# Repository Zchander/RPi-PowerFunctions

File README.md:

RPi-PowerFunctions
==================

A project to send commands over IR to a LEGO PowerFunctions receiver using an Raspberry Pi, I2C and an ATtiny2313

The Eagle project files have been added (including the PCB designs), as are the XMLRPC server files.

I'll try to update/create READMEs for the sub folders in the near future. Unfortunately my documenting skills are a bit 'subzero'

For this project I would like to thank a few people, who I will list down here. Please note that the order is random!
- Jurriaan Pruis (https://github.com/jurriaan/) for his project which gave me the idea(s)
- Dick de Wit (www.dansendelichtjes.nl) who helped me refresh some of my electronics skills
- A few from www.avrfreaks.net, some I will mention explicit:
- - kk6gm for inspiring me to NOT use _delay_ms/_delay_us in my code, but to use interrupts
- - kartman for his tutorial on multitasking on the AVR environment
- - david.prentice for directing me into a bug I introduced myself during code cleanup
- - clawson for his inspiring and helpful comments overall

(If I forgot someone, please let me know so I can include you on the list)

Xander

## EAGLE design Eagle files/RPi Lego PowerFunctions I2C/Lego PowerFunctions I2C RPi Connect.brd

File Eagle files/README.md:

The Eagle file(s) are made with version 7.2.0 and only contain the schematics. The PCB designs still have to be made.

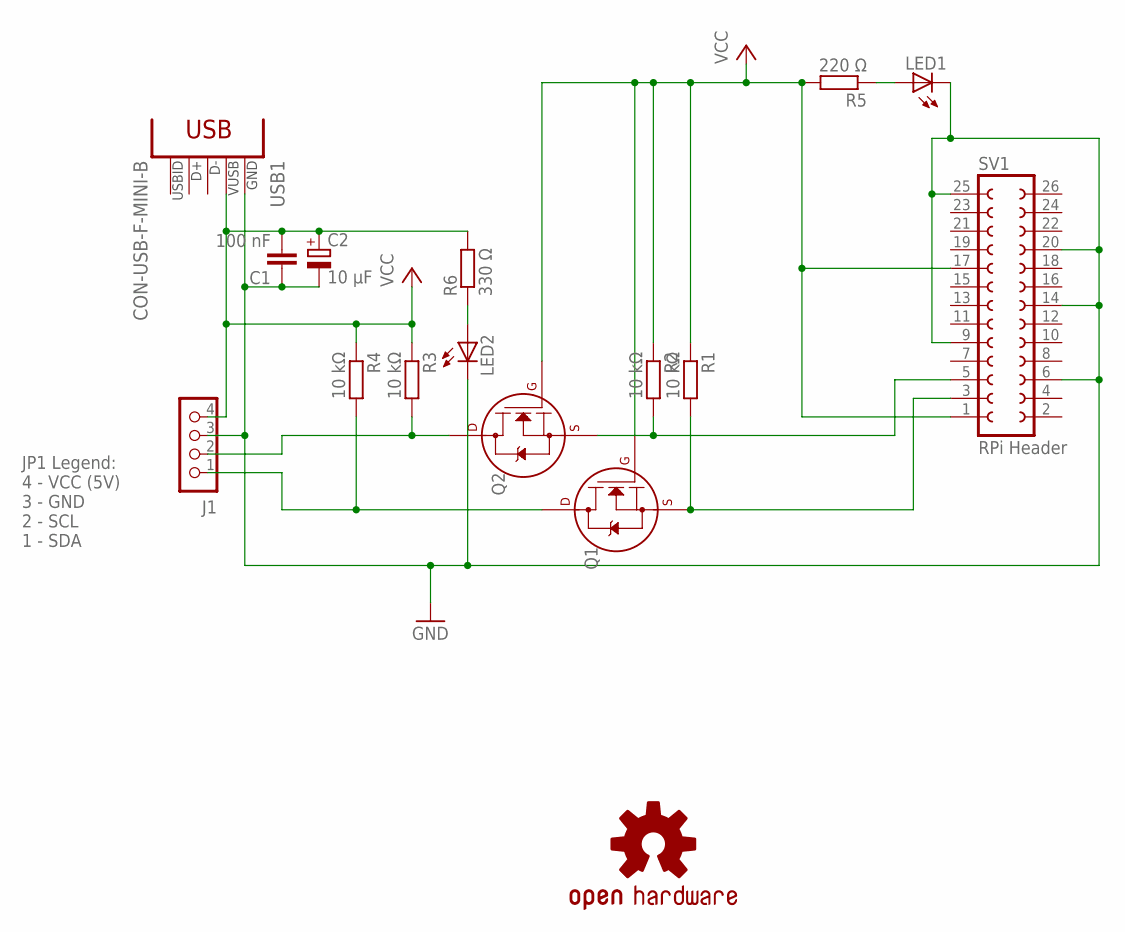
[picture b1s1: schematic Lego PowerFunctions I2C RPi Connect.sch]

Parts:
C1: 100 nF; C025-025X050
C2: 10 µF; E2,5-6
J1: CON_HEADER_1X04; M1X4
LED1, LED2: LED3MM
LOGO1: OSHW-LOGOL; OSHW-LOGO-L
Q1, Q2: 2N7000_TO92; TO-92
R1, R2, R3, R4: 10 kΩ; 0207/10
R5: 220 Ω; 0207/10
R6: 330 Ω; 0207/10
SV1: RPi Header; FE13-2
USB1: CON-USB-F-MINI-B; CONN_USB_MINI-B

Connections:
GND: C1.1, C2.-, J1.3, LED1.K (C), LED2.K (C), SV1.6, SV1.9, SV1.14, SV1.20, SV1.25, USB1.GND
unnamed: LED1.A, R5.1
unnamed: LED2.A, R6.1
unnamed: Q1.1 (S), R1.2, SV1.3
SCL_HV: J1.2, Q2.3 (D), R3.2
SCL_LV: Q2.1 (S), R2.2, SV1.5
SDA_HV: J1.1, Q1.3 (D), R4.2
VCC_HV: C1.2, C2.+, J1.4, R3.1, R4.1, R6.2, USB1.VUSB
VCC_LV: Q1.2 (G), Q2.2 (G), R1.1, R2.1, R5.2, SV1.1, SV1.17

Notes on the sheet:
JP1 Legend: 4 - VCC (5V) 3 - GND 2 - SCL 1 - SDA

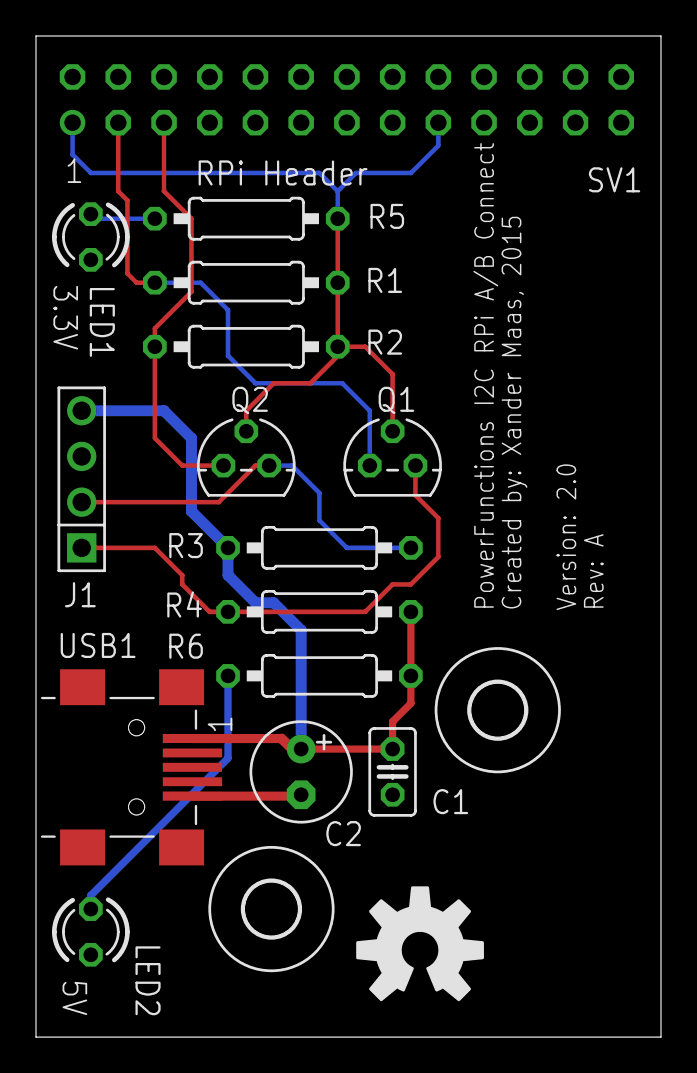
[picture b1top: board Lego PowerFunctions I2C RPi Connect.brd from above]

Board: 2 copper layers, 34.7 x 55.6 mm, 18 parts (1 on the bottom side), 9 nets.

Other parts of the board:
U$1, U$3: 3,0

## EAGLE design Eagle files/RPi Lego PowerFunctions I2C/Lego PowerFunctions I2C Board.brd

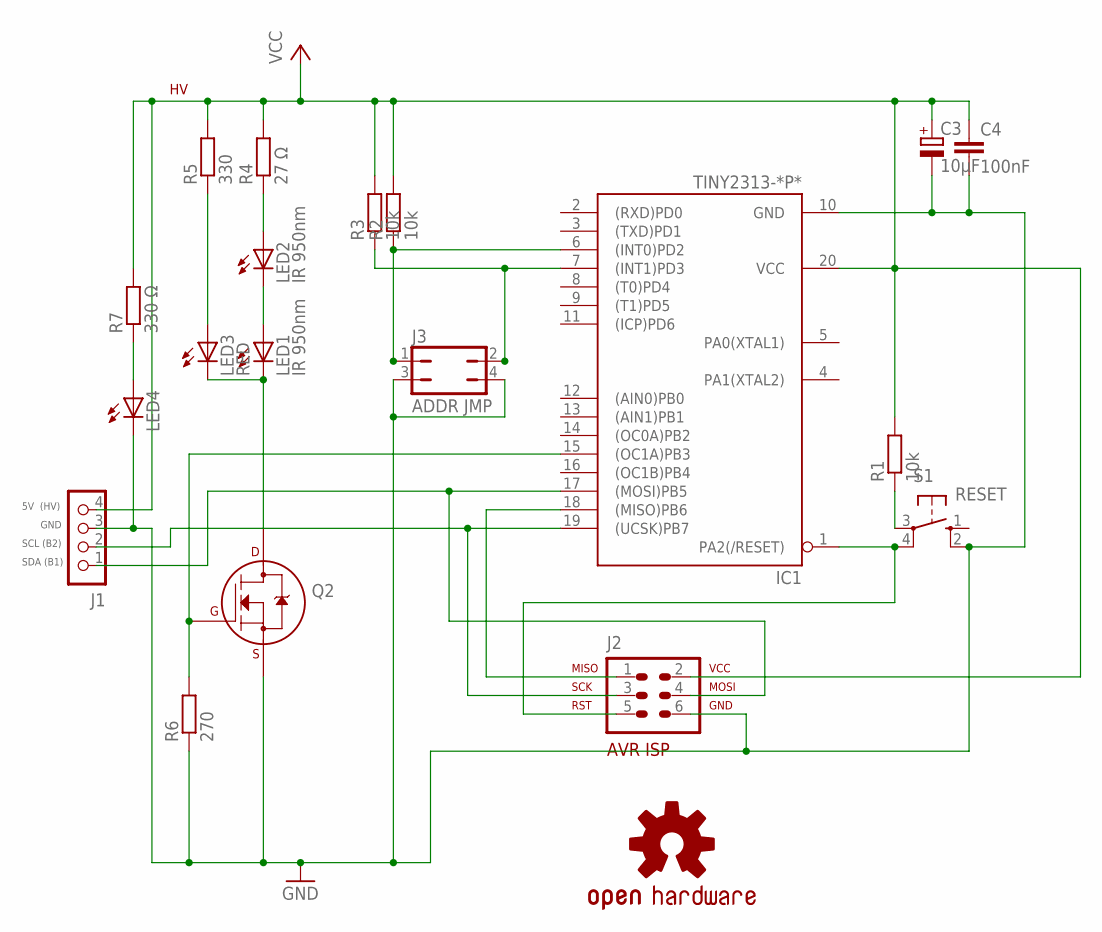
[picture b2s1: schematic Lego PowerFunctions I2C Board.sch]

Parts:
C3: 10µF; E2,5-6
C4: 100nF; C025-025X050
IC1: TINY2313-*P*; DIL20
J1: CON_HEADER_1X04; M1X4
J2: AVR-ISP-6VERT; AVR-ISP-6
J3: ADDR JMP; JP2Q
LED1, LED2: IR 950nm; LED5MM
LED3: RED; LED3MM
LED4: LED3MM
LOGO1: OSHW-LOGOM; OSHW-LOGO-M
Q2: 2N7000_TO92; TO-92
R1, R2, R3: 10k; 0207/10
R4: 27 Ω; 0207/10
R5: 330; 0207/10
R6: 270; 0207/10
R7: 330 Ω; 0207/10
S1: RESET; B3F-10XX

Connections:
GND: C3.-, C4.2, IC1.10 (GND), J1.3, J2.6, J3.3, J3.4, LED4.K (C), Q2.1 (S), R6.1, S1.2 (S1)
I2CADDRH: IC1.7 ((INT1)PD3), J3.2, R3.1
I2CADDRL: IC1.6 ((INT0)PD2), J3.1, R2.1
MISO: IC1.18 ((MISO)PB6), J2.1
MOSI: IC1.17 ((MOSI)PB5), J1.1, J2.4
unnamed: LED4.A, R7.1
unnamed: R1.1, S1.3
unnamed: LED2.A, R4.1
unnamed: LED3.A, R5.1
unnamed: LED1.A, LED2.K (C)
unnamed: LED1.K (C), LED3.K (C), Q2.3 (D)
unnamed: IC1.15 ((OC1A)PB3), Q2.2 (G), R6.2
RST: IC1.1 (PA2(/RESET)), J2.5, S1.4 (P1)
SCL: IC1.19 ((UCSK)PB7), J1.2, J2.3
VCC: C3.+, C4.1, IC1.20 (VCC), J1.4, J2.2, R1.2, R2.2, R3.2, R4.2, R5.2, R7.2

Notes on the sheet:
5V (HV)
SDA (B1)
SCL (B2)
GND

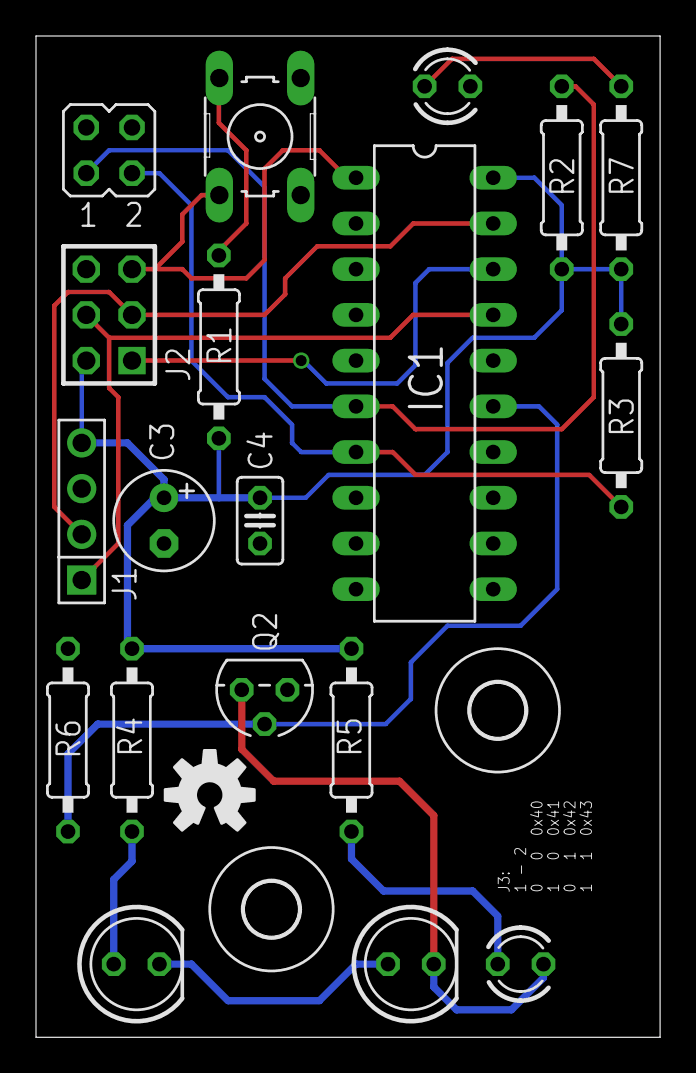
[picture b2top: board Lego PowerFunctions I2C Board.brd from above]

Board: 2 copper layers, 34.7 x 55.6 mm, 22 parts (0 on the bottom side), 15 nets.

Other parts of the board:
U$1, U$2: 3,0

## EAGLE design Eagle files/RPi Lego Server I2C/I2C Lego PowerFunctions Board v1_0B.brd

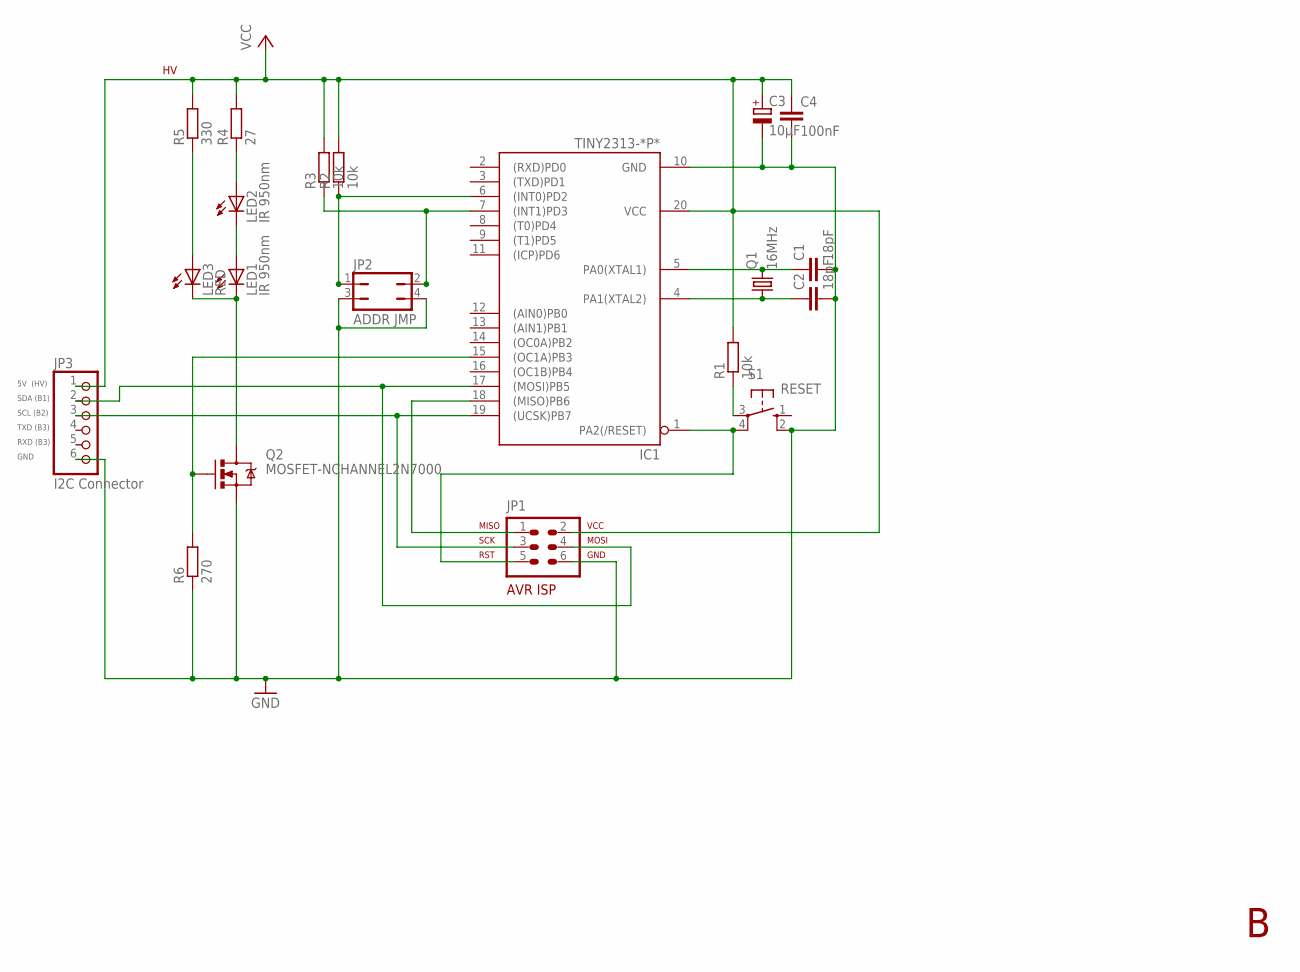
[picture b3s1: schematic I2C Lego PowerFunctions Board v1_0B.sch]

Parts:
C1, C2: 18pF; C025-025X050
C3: 10µF; E2,5-6
C4: 100nF; C050-030X075
IC1: TINY2313-*P*; DIL20
JP1: AVR-ISP-6VERT; AVR-ISP-6
JP2: ADDR JMP; JP2Q
JP3: I2C Connector; 1X06
LED1, LED2: IR 950nm; LED5MM
LED3: RED; LED3MM
Q1: 16MHz; HC49/S
Q2: MOSFET-NCHANNEL2N7000; TO-92
R1, R2, R3: 10k; 0207/10
R4: 27; 0207/10
R5: 330; 0207/10
R6: 270; 0207/10
S1: RESET; B3F-10XX

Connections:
GND: C1.2, C2.2, C3.-, C4.2, IC1.10 (GND), JP1.6, JP2.3, JP2.4, JP3.6, Q2.1 (S), R6.1, S1.2 (S1)
I2CADDRH: IC1.7 ((INT1)PD3), JP2.2, R3.1
I2CADDRL: IC1.6 ((INT0)PD2), JP2.1, R2.1
MISO: IC1.18 ((MISO)PB6), JP1.1
MOSI: IC1.17 ((MOSI)PB5), JP1.4, JP3.2
unnamed: R1.1, S1.3
unnamed: LED2.A, R4.1
unnamed: LED3.A, R5.1
unnamed: LED1.A, LED2.K (C)
unnamed: LED1.K (C), LED3.K (C), Q2.3 (D)
unnamed: IC1.15 ((OC1A)PB3), Q2.2 (G), R6.2
RST: IC1.1 (PA2(/RESET)), JP1.5, S1.4 (P1)
SCL: IC1.19 ((UCSK)PB7), JP1.3, JP3.3
VCC: C3.+, C4.1, IC1.20 (VCC), JP1.2, JP3.1, R1.2, R2.2, R3.2, R4.2, R5.2
XTAL1: C2.1, IC1.4 (PA1(XTAL2)), Q1.1
XTAL2: C1.1, IC1.5 (PA0(XTAL1)), Q1.2

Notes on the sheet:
5V (HV)
SDA (B1)
SCL (B2)
GND
TXD (B3)
RXD (B3)

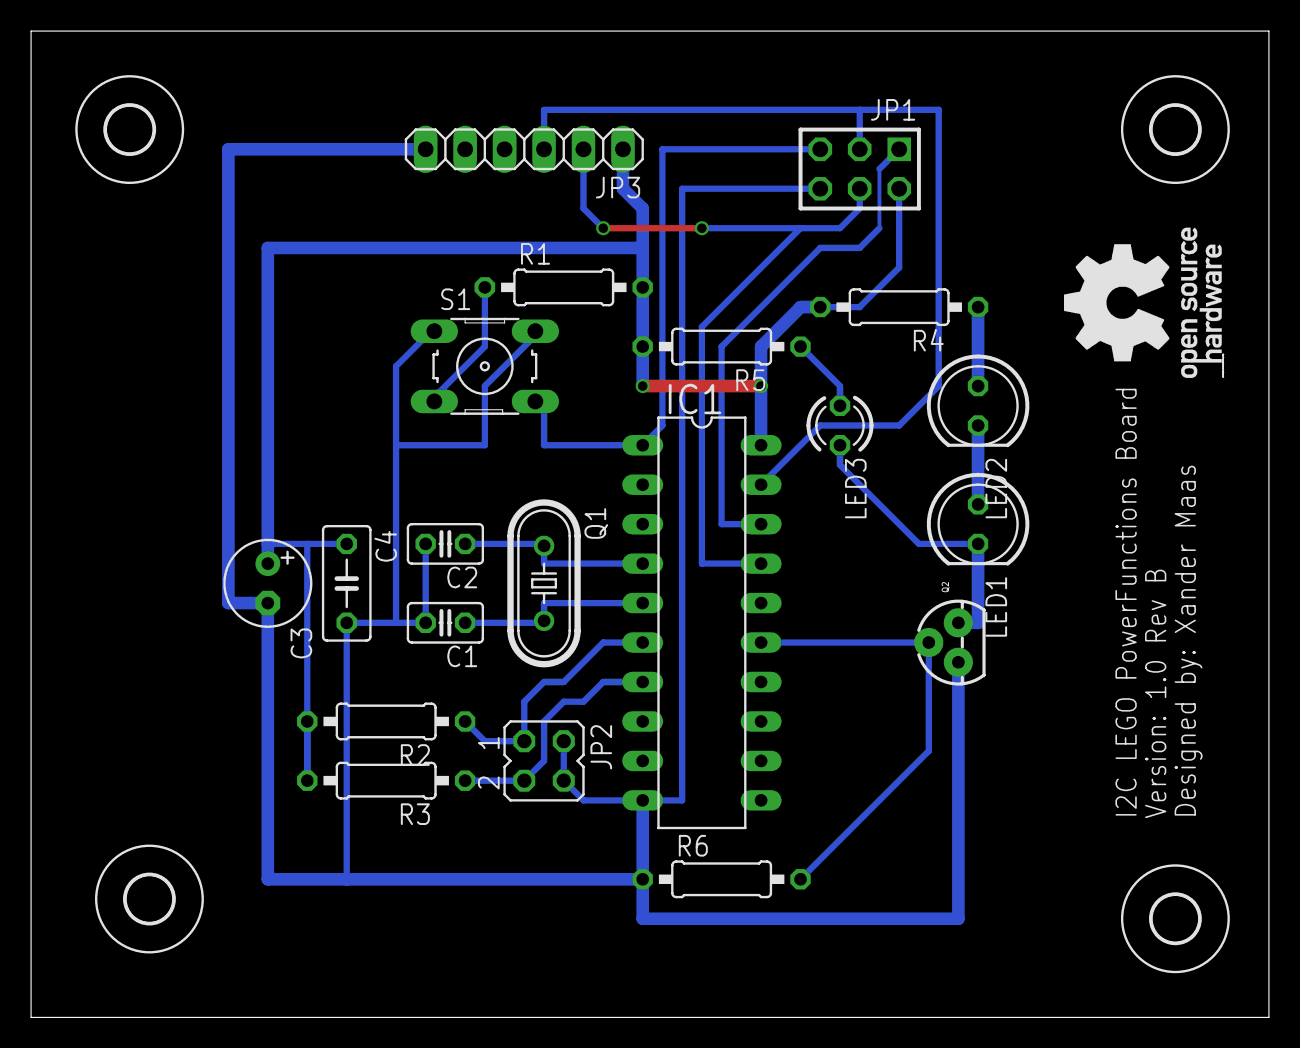
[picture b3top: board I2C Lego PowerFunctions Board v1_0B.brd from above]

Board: 2 copper layers, 79.7 x 63.5 mm, 24 parts (0 on the bottom side), 16 nets.

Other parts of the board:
U$2, U$3, U$4, U$5: 3,0

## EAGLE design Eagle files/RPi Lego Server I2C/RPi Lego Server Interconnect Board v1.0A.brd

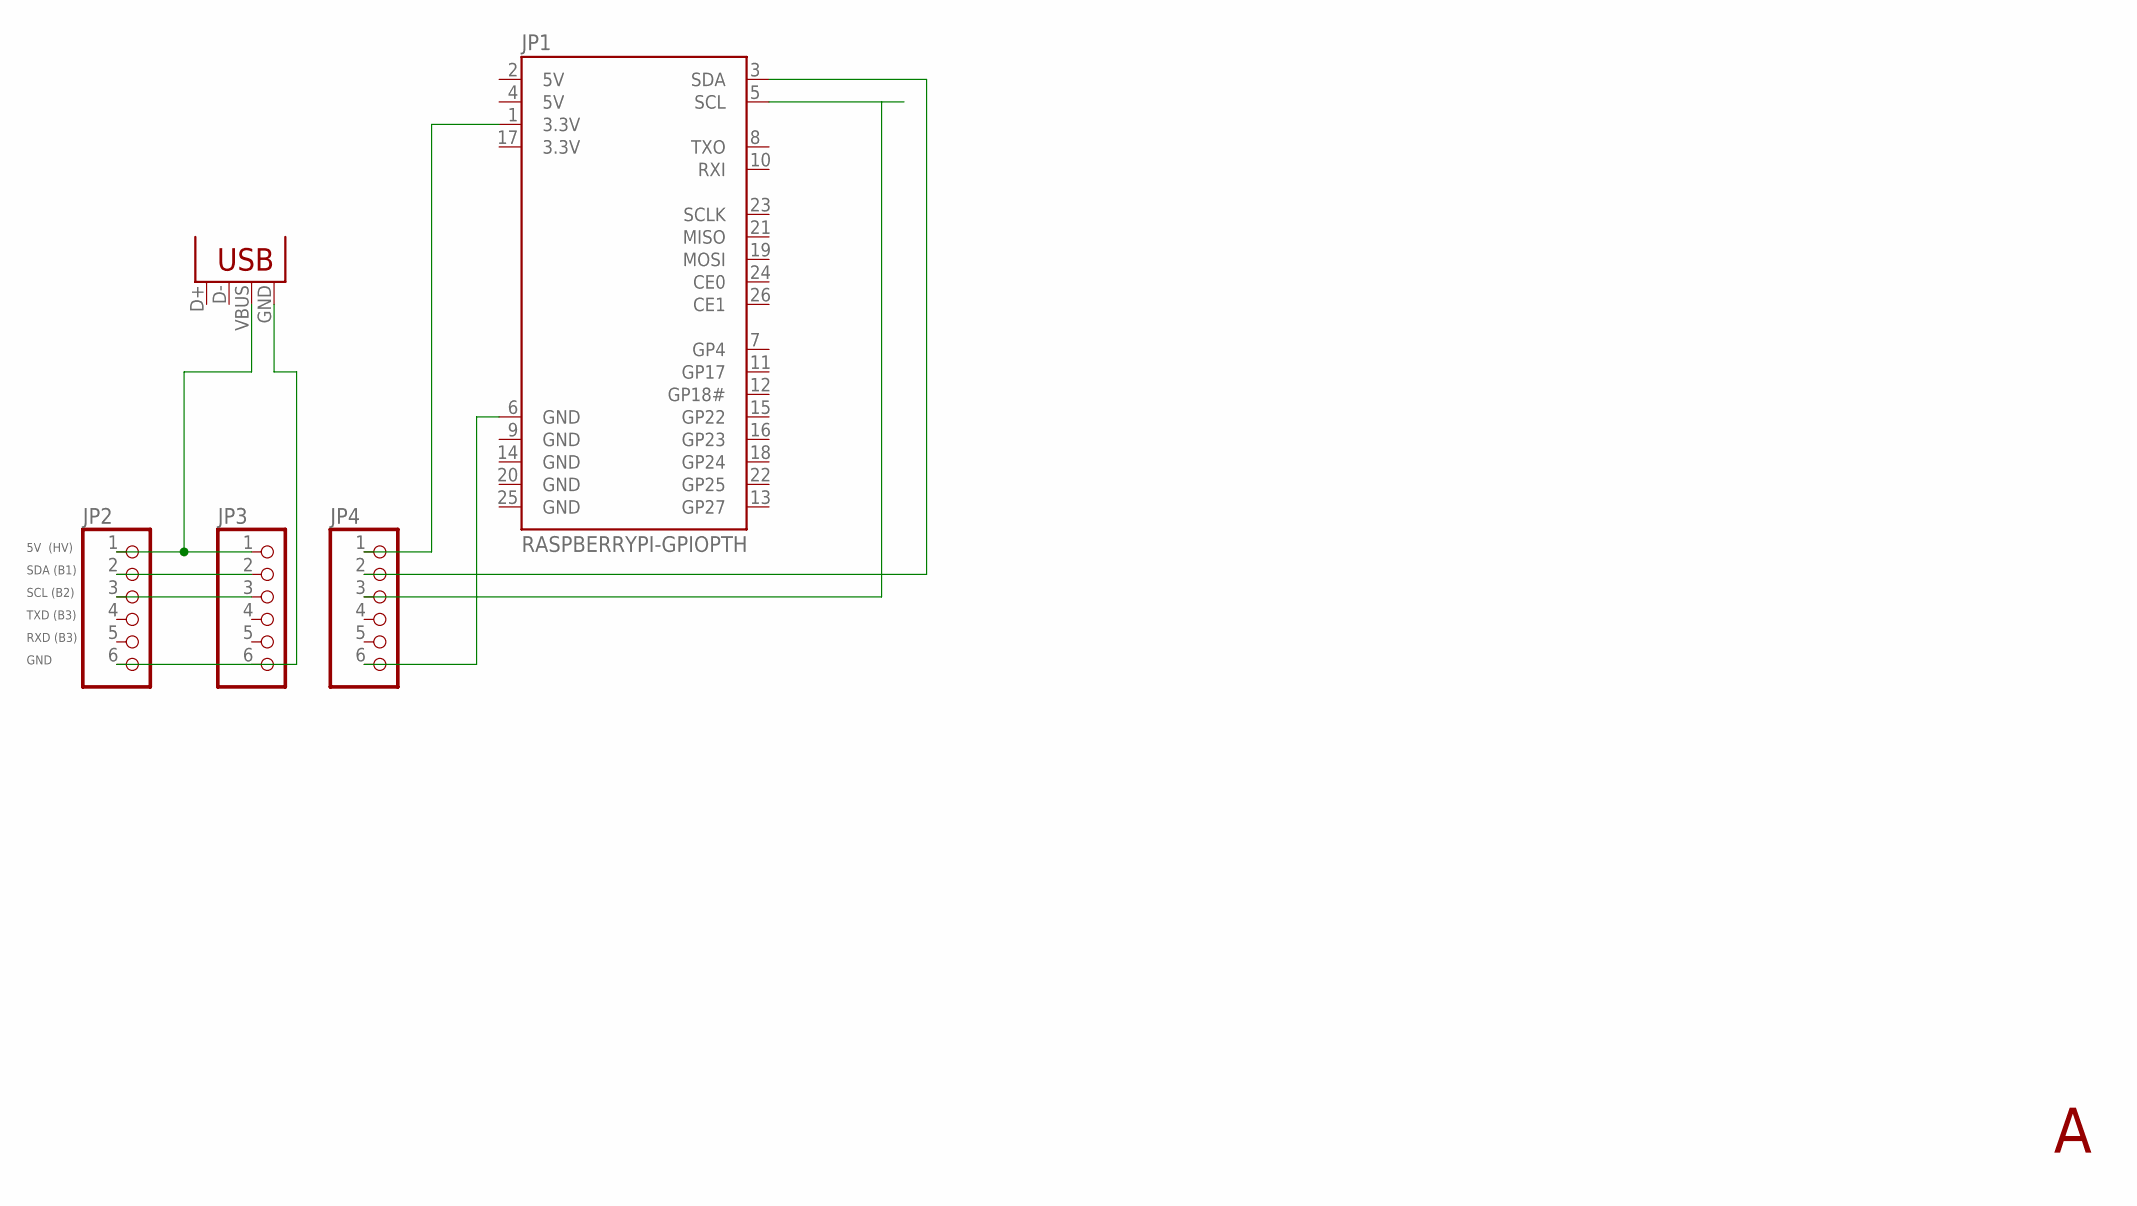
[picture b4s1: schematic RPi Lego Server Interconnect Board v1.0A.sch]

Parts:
JP1: RASPBERRYPI-GPIOPTH; 2X13-SHROUDED
JP2, JP3, JP4: PINHD-1X6; 1X06
JP5: USB-B; USB-B-PTH

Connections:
3.3V: JP1.17 (3.3V)
5V: JP1.2 (5V), JP1.4 (5V)
GND: JP1.9 (GND), JP1.14 (GND), JP1.20 (GND), JP1.25 (GND)
unnamed: JP1.3 (SDA), JP4.2
unnamed: JP1.5 (SCL), JP4.3
unnamed: JP1.6 (GND), JP4.6
unnamed: JP2.6, JP3.6, JP5.GND
unnamed: JP2.1, JP3.1, JP5.VBUS
unnamed: JP2.2, JP3.2
unnamed: JP2.3, JP3.3
unnamed: JP1.1 (3.3V), JP4.1

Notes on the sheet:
5V (HV)
SDA (B1)
SCL (B2)
GND
TXD (B3)
RXD (B3)

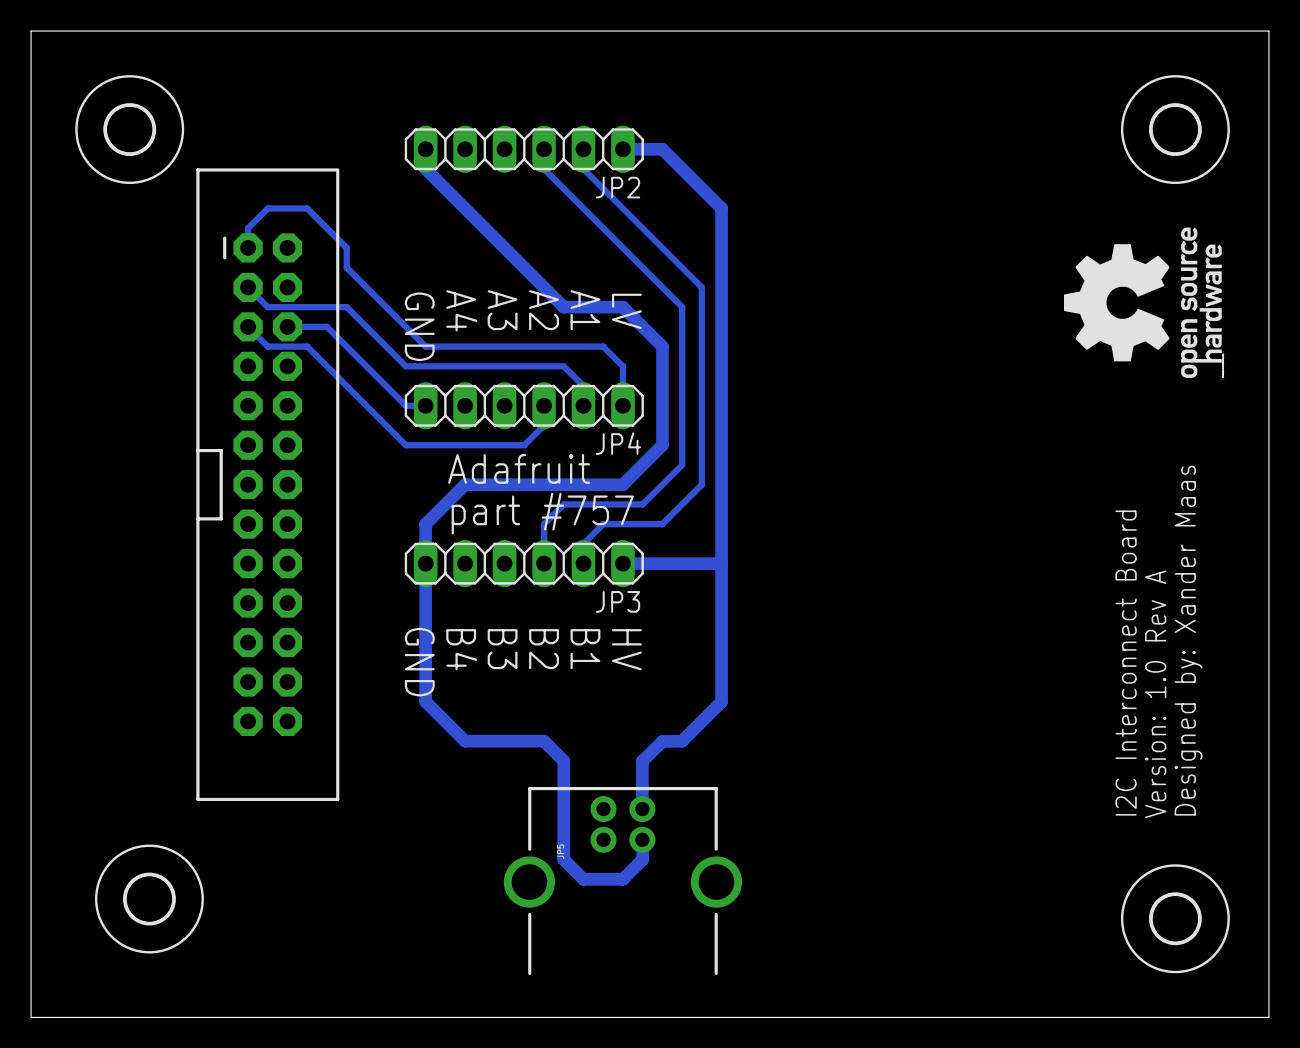
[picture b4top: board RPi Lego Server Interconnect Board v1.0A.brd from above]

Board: 2 copper layers, 79.7 x 63.5 mm, 9 parts (0 on the bottom side), 10 nets.

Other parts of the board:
U$2, U$3, U$4, U$5: 3,0

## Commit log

2014-12-26 Update README.md
    Added additional information about the project
2014-12-26 Added ATtiny2313 firmware
    Version 0.1 of the ATtiny2313 firmware added.
    NOTE: This firmware is for a test environment WITHOUT a 16MHz crystal
2014-12-26 Eagle file(s) added
    These are the Eagle files for the project. The files are made with
    version 7.2.0 and contain at the moment just the schematics.
    I still have to create the PCB layout(s)
2014-12-26 Create README.md
    Initial creation of README file
2014-12-29 Uploaded new schematics, both interconnect board and IR board. USB connector (for power) has been moved to interconnect board. Also added routed PCB designs
2014-12-30 Added basic XMLRPC server and test script
    XMLRPC server and test script are written in python.
    Expect a lot of (and I really mean a lot) debugging logs.
    When using the test script, edit it to reflect your settings/addresses
    etc.
2015-01-15 Some minor corrections in PCB/schematic design
    Corrected JP2 (I2C) Address headers, so they are oriented correctly
    Also renamed the PowerFunctions board to reflect it's actual function:
    I2C Lego PowerFunctions Board
2015-01-15 Added a .gitignore
2015-01-21 Updated xmlrpcServer and xmlrpc_debug
    xmlrpcServer (v1.0.1):
    Added an additional test for the checksum nibble of command. Also added
    a test to check if the command is being sent to the correct channel
    xmlrpc_debug (v1.0.1):
    Recreated version, with commandline options. Also cleaned (some) code.
    Seems a good debug/test util to me ;)
2015-01-30 Checksum/toggle change
    Now Bit 0 (MSB) in nibble 1 will be properly toggled. It also
    recalculates the checksum (nibble 4)
    Also bumped firmware version to 0.1.0
2015-01-31 Scratch interface added, firmware updates
    - Added a Scratch (1.4) interface/python script, so we can control
    Lego Powerfunctions from within Scratch (documentation not done yet,
    read source ;))
    - Added a new firmware which *should* support Combo PWM mode. (Still
    some issues with channel 2+)
2015-01-31 Updated .gitignore
2015-02-01 Comments cleaned
    Cleaned some comments
2015-02-01 More comment cleanup
2015-02-05 Added Scratch 1.4 test files
    - Start the xmlrpcServer on your Raspberry Pi (e.g. ./main.py)
    - Start the ScratchClient on your client or Raspberry Pi
    ./main -s 192.168.32.11 -x http://127.0.0.1:9000
    -s is the IP address of the computer running Scratch
    -x is the URL for the xmlrpcServer e.g. http://127.0.0.1:9000 if you
    are
2015-02-05 Added a new version of the board
    Added a new board version, this one should fit a Raspberry PI A or B
    model.
    Also added impressions of the boards, rendered in SketchUp
2015-02-14 Raspberry Pi board detection code updated
    Added a quick (and dirty) hack to identify the A+, B+, Compute Module
    and Raspberry Pi 2 B models.

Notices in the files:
parts and their libraries:
SparkFun-Aesthetics: Licensing: Creative Commons ShareAlike 4.0 International - https://creativecommons.org/licenses/by-sa/4.0
